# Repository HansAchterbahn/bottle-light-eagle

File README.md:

# Bottle Light: Eagle Data (PCB)

Bottle Light is a coaster that make your bottle glow in all colors of the rainbow. More information about the Bottle Light project can be found in the main repository: [bottle-light](https://github.com/HansAchterbahn/bottle-light)

In this Repository you can find the shematics and board layouts created in Eagle.

*Fork me and have fun!*

## Schematic

## Board

## 3D View (Fusion360)

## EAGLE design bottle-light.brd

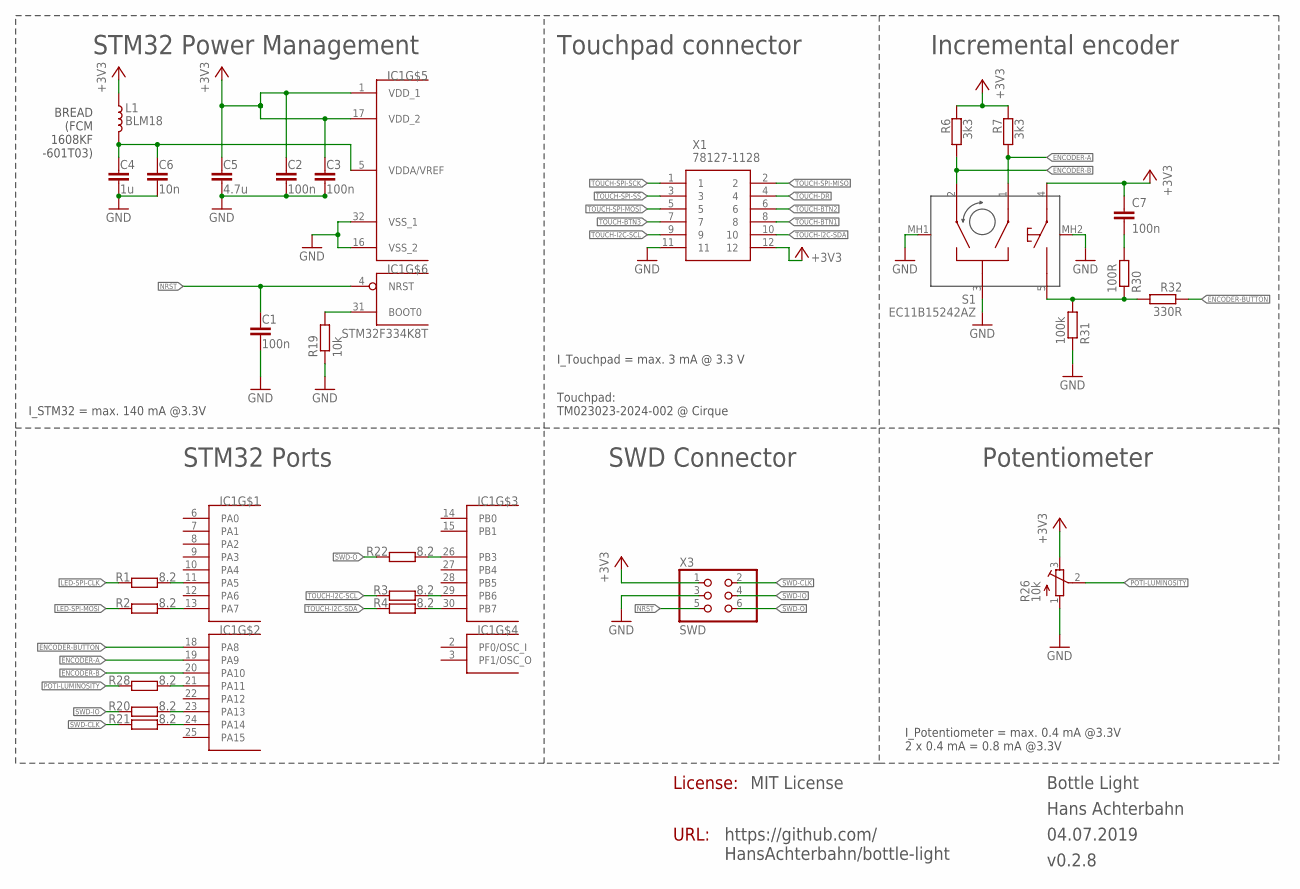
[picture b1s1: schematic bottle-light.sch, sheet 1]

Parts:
C1, C2, C3: 100n; C0603K
C4: 1u; C0603K
C5: 4.7u; C0603K
C6: 10n; C0603K
C7: 100n; C0603; MOUSER 581-0603YC104J
IC1: STM32F334K8T; LQFP32-7X7
L1: BLM18; L0603; MOUSER 81-BLM18KG601SN1D
R1, R2, R3, R4, R20, R21, R22, R28: 8.2; R0603
R6, R7: 3k3; R0603; MOUSER 71-CRCW06032K70FKEAC
R19: 10k; R0603
R26: 10k; RK0971110
R30: 100R; R0603; MOUSER 71-CRCW0603-100-E3
R31: 100k; R0603; MOUSER 71-CRCW0603-100K-E3
R32: 330R; R0603; MOUSER 71-CRCW0603-330-E3
S1: EC11B15242AZ; MPN EC11B15242AZ; MOUSER 688-EC11B15242AE
X1: 78127-1128; 781271128
X3: SWD; 2X03SMD; MOUSER 855-M20-8760342

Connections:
!TOUCH-SPI-SS: X1.3
+3V3: C2.1, C3.1, C5.1, C7.1, IC1.1 (VDD_1), IC1.17 (VDD_2), L1.1, R6.1, R7.1, R26.3 (E), S1.4 (D), X1.12, X3.1; also elsewhere on the board
ENCODER-A: IC1.19 (PA9), R7.2, S1.1 (A)
ENCODER-B: IC1.20 (PA10), R6.2, S1.2 (B)
ENCODER-BUTTON: IC1.18 (PA8), R32.1
GND: C1.2, C2.2, C3.2, C4.2, C5.2, C6.2, IC1.16 (VSS_2), IC1.32 (VSS_1), R19.1, R26.1 (A), R31.1, S1.3 (C), S1.MH1, S1.MH2, X1.11, X3.3; also elsewhere on the board
LED-SPI-CLK: R1.1; also elsewhere on the board
LED-SPI-MOSI: R2.1; also elsewhere on the board
unnamed: IC1.24 (PA14), R21.2
unnamed: IC1.11 (PA5), R1.2
unnamed: IC1.13 (PA7), R2.2
unnamed: IC1.29 (PB6), R3.2
unnamed: IC1.30 (PB7), R4.2
unnamed: IC1.21 (PA11), R28.2
unnamed: C4.1, C6.1, IC1.5 (VDDA/VREF), L1.2
unnamed: IC1.31 (BOOT0), R19.2
unnamed: IC1.23 (PA13), R20.2
unnamed: IC1.26 (PB3), R22.2
unnamed: R30.1, R31.2, R32.2, S1.5 (E)
unnamed: C7.2, R30.2
NRST: C1.1, IC1.4 (NRST), X3.5
POTI-LUMINOSITY: R26.2 (S), R28.1
SWD-CLK: R21.1, X3.2
SWD-IO: R20.1, X3.4
SWD-O: R22.1, X3.6
TOUCH-BTN1: X1.8
TOUCH-BTN2: X1.6
TOUCH-BTN3: X1.7
TOUCH-DR: X1.4
TOUCH-I2C-SCL: R3.1, X1.9
TOUCH-I2C-SDA: R4.1, X1.10
TOUCH-SPI-MISO: X1.2
TOUCH-SPI-MOSI: X1.5
TOUCH-SPI-SCK: X1.1

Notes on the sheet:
STM32 Power Management
STM32 Ports
Incremental encoder
SWD Connector
Potentiometer
I_Potentiometer = max. 0.4 mA @3.3V 2 x 0.4 mA = 0.8 mA @3.3V
I_STM32 = max. 140 mA @3.3V
License:
BREAD (FCM 1608KF -601T03)
Touchpad connector
I_Touchpad = max. 3 mA @ 3.3 V
Touchpad: TM023023-2024-002 @ Cirque
https://github.com/ HansAchterbahn/bottle-light
URL:

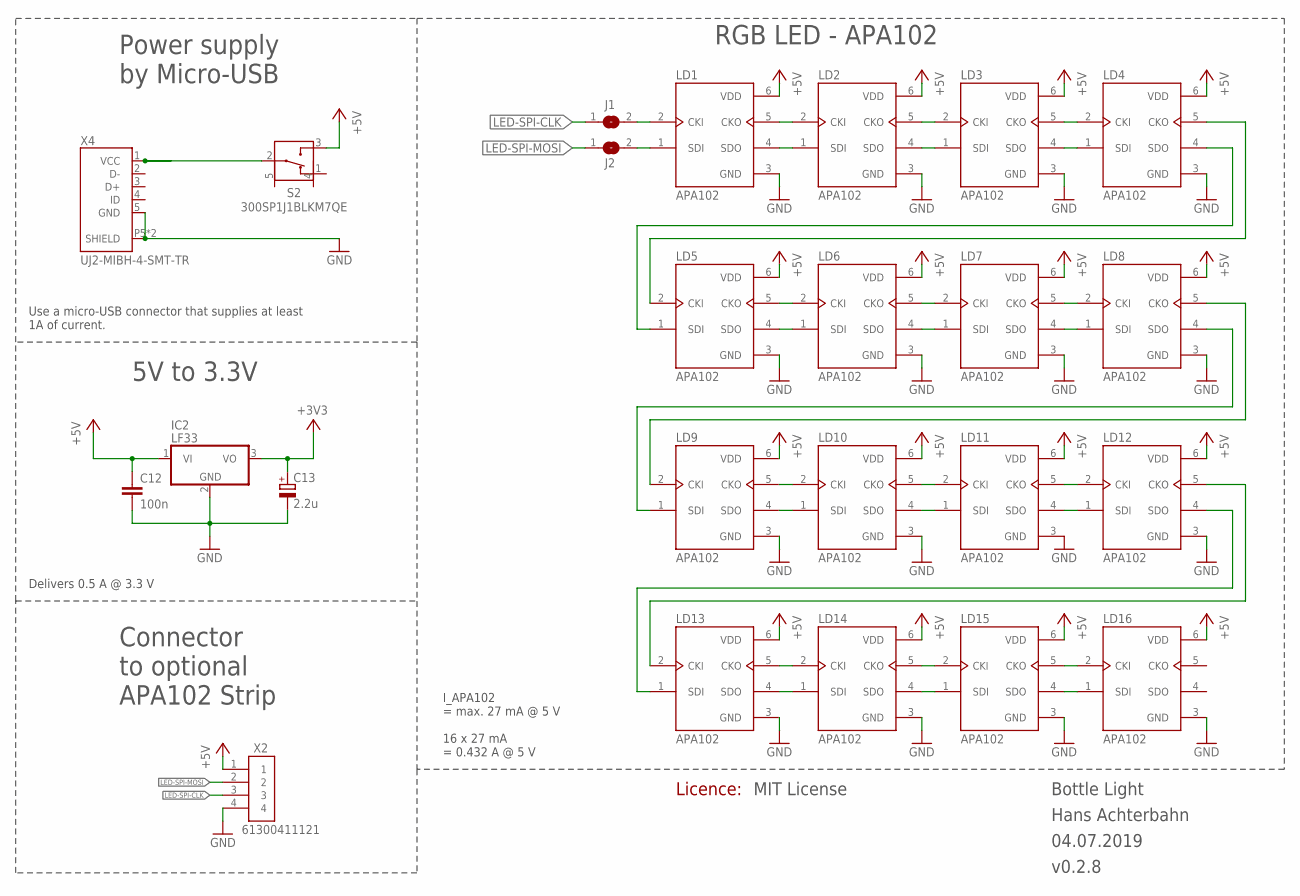
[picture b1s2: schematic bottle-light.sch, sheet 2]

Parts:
C12: 100n; C0603
C13: 2.2u; 153CLV-0505
IC2: LF33; TO220H
J1, J2: SJ
LD1, LD2, LD3, LD4, LD5, LD6, LD7, LD8, LD9, LD10, LD11, LD12, LD13, LD14, LD15, LD16: APA102; APA102C-5050
S2: 300SP1J1BLKM7QE
X2: 61300411121
X4: UJ2-MIBH-4-SMT-TR; CUIINC_UJ2-MIBH-4-SMT-TR-2; MOUSER 490-UJ2-MIBH-4-SMT

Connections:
5V-IN: S2.2 (IN), X4.1 (VCC)
+3V3: C13.+, IC2.3 (VO); also elsewhere on the board
+5V: C12.1, IC2.1 (VI), LD1.6 (VDD), LD2.6 (VDD), LD3.6 (VDD), LD4.6 (VDD), LD5.6 (VDD), LD6.6 (VDD), LD7.6 (VDD), LD8.6 (VDD), LD9.6 (VDD), LD10.6 (VDD), LD11.6 (VDD), LD12.6 (VDD), LD13.6 (VDD), LD14.6 (VDD), LD15.6 (VDD), LD16.6 (VDD), S2.3 (OUT1), X2.1
GND: C12.2, C13.-, IC2.2 (GND), LD1.3 (GND), LD2.3 (GND), LD3.3 (GND), LD4.3 (GND), LD5.3 (GND), LD6.3 (GND), LD7.3 (GND), LD8.3 (GND), LD9.3 (GND), LD10.3 (GND), LD11.3 (GND), LD12.3 (GND), LD13.3 (GND), LD14.3 (GND), LD15.3 (GND), LD16.3 (GND), X2.4, X4.5 (GND), X4.P5 (SHIELD), X4.P6 (SHIELD); also elsewhere on the board
LED-SPI-CLK: J1.1, X2.3; also elsewhere on the board
LED-SPI-MOSI: J2.1, X2.2; also elsewhere on the board
unnamed: J1.2, LD1.2 (CKI)
unnamed: J2.2, LD1.1 (SDI)
unnamed: LD1.5 (CKO), LD2.2 (CKI)
unnamed: LD1.4 (SDO), LD2.1 (SDI)
unnamed: LD2.5 (CKO), LD3.2 (CKI)
unnamed: LD2.4 (SDO), LD3.1 (SDI)
unnamed: LD3.5 (CKO), LD4.2 (CKI)
unnamed: LD3.4 (SDO), LD4.1 (SDI)
unnamed: LD4.5 (CKO), LD5.2 (CKI)
unnamed: LD4.4 (SDO), LD5.1 (SDI)
unnamed: LD5.5 (CKO), LD6.2 (CKI)
unnamed: LD5.4 (SDO), LD6.1 (SDI)
unnamed: LD6.5 (CKO), LD7.2 (CKI)
unnamed: LD6.4 (SDO), LD7.1 (SDI)
unnamed: LD7.5 (CKO), LD8.2 (CKI)
unnamed: LD7.4 (SDO), LD8.1 (SDI)
unnamed: LD8.5 (CKO), LD9.2 (CKI)
unnamed: LD8.4 (SDO), LD9.1 (SDI)
unnamed: LD9.5 (CKO), LD10.2 (CKI)
unnamed: LD9.4 (SDO), LD10.1 (SDI)
unnamed: LD10.5 (CKO), LD11.2 (CKI)
unnamed: LD10.4 (SDO), LD11.1 (SDI)
unnamed: LD11.5 (CKO), LD12.2 (CKI)
unnamed: LD11.4 (SDO), LD12.1 (SDI)
unnamed: LD12.5 (CKO), LD13.2 (CKI)
unnamed: LD12.4 (SDO), LD13.1 (SDI)
unnamed: LD13.5 (CKO), LD14.2 (CKI)
unnamed: LD13.4 (SDO), LD14.1 (SDI)
unnamed: LD14.5 (CKO), LD15.2 (CKI)
unnamed: LD14.4 (SDO), LD15.1 (SDI)
unnamed: LD15.5 (CKO), LD16.2 (CKI)
unnamed: LD15.4 (SDO), LD16.1 (SDI)

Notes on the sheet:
Power supply by Micro-USB
5V to 3.3V
RGB LED - APA102
Delivers 0.5 A @ 3.3 V
Use a micro-USB connector that supplies at least 1A of current.
I_APA102 = max. 27 mA @ 5 V 16 x 27 mA = 0.432 A @ 5 V
Licence:
Connector to optional APA102 Strip

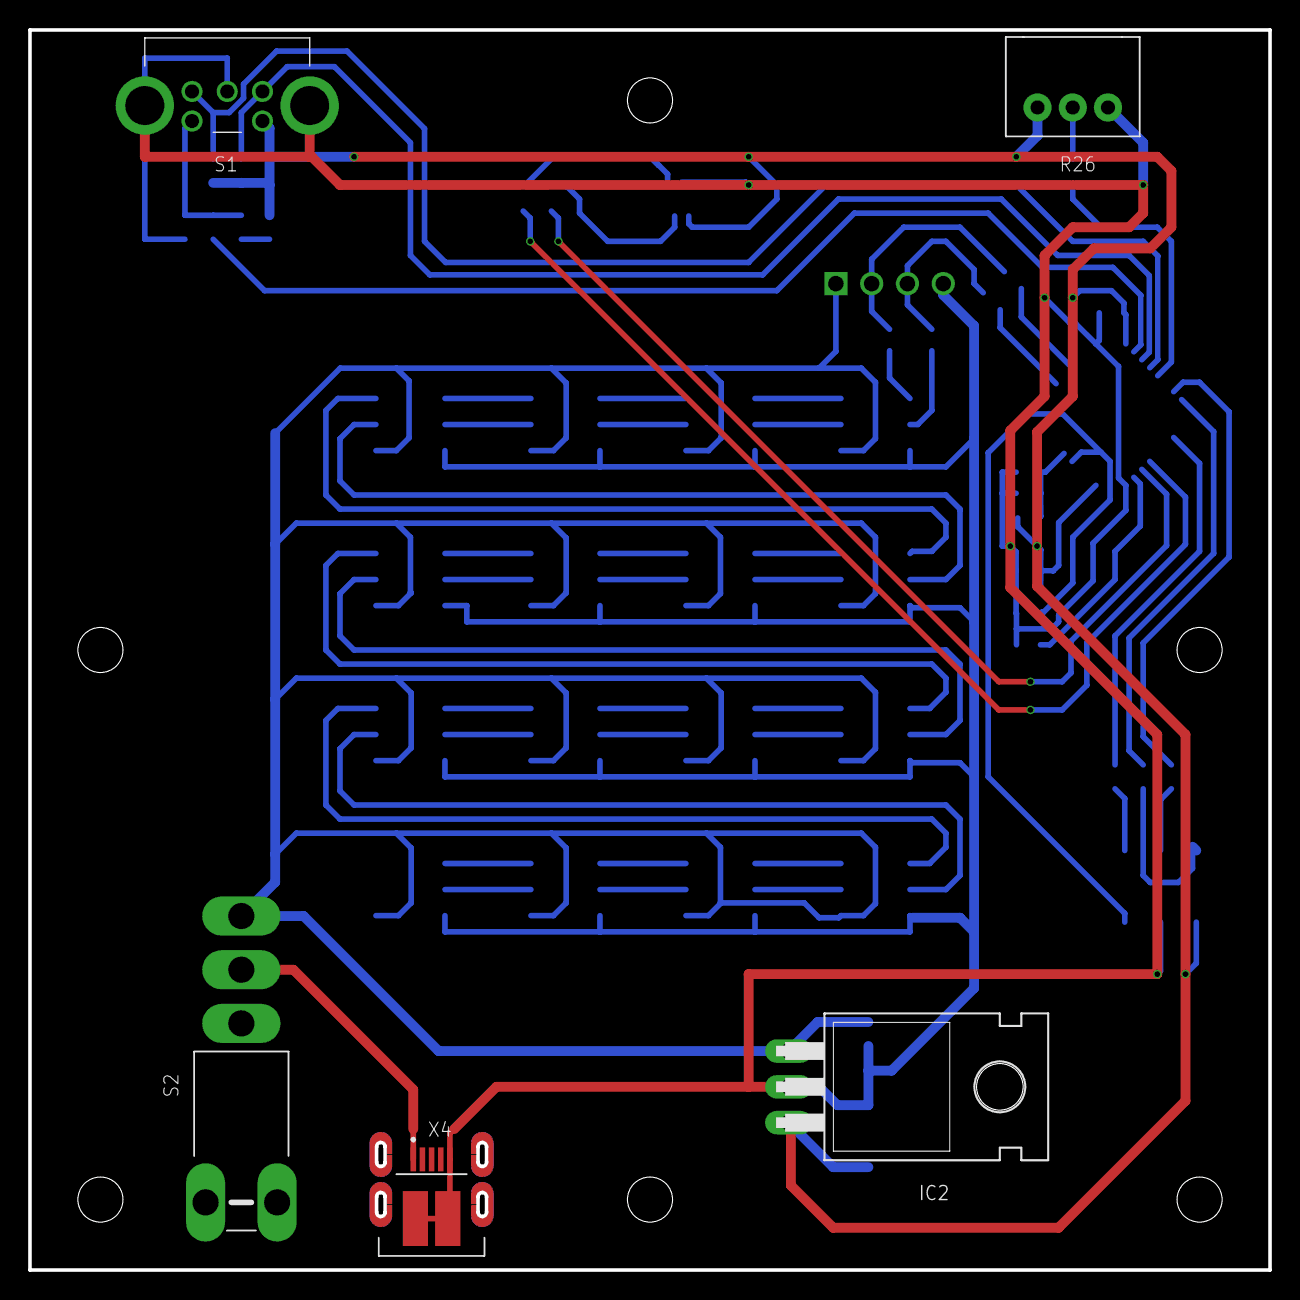
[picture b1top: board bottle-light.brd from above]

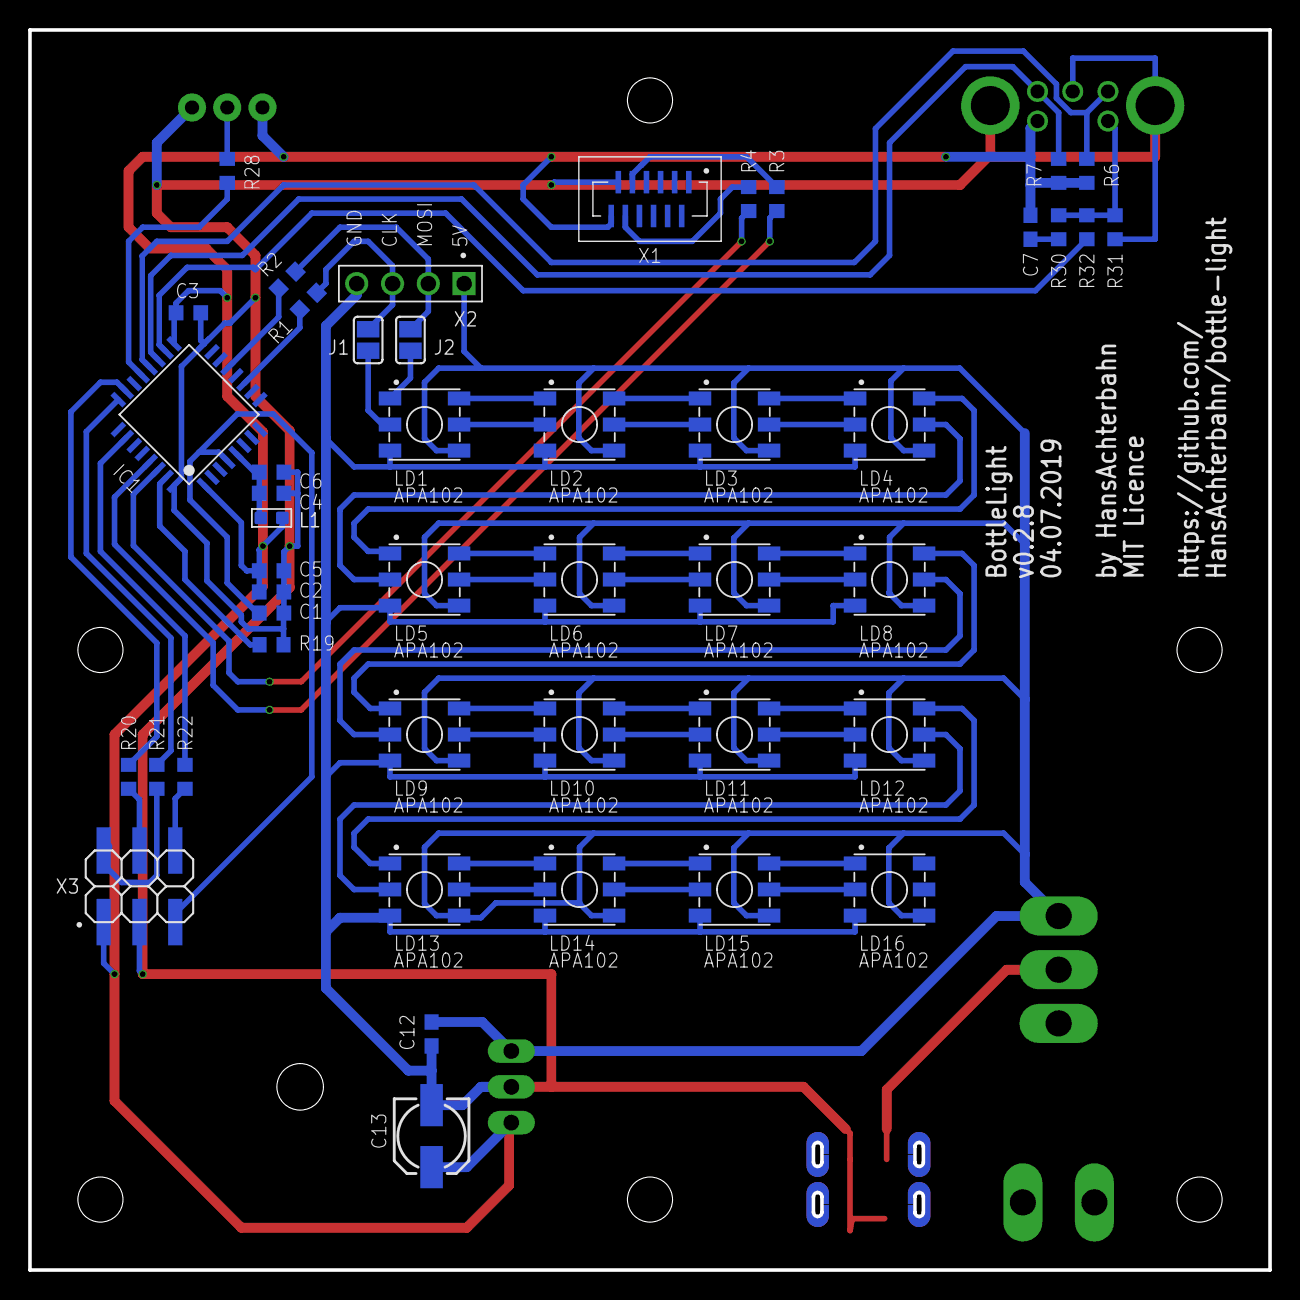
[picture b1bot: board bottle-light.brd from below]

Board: 2 copper layers, 88.0 x 88.0 mm, 52 parts (46 on the bottom side), 60 nets.

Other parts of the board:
U$1: A4L-LOC

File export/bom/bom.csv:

Qty;Value;Device;Package;Parts;Description;ALLIED_NUMBER;ALLIED_PRICE-STOCK;CREATED_BY;DESCRIPTION;DIGI_KEY_PART_NUMBER;HEIGHT;MANUFACTURER;MF;MFN;MOUSER;RS-ONLINE
2;;SJ;SJ;J1, J2;SMD solder JUMPER;;;;;;;;;;;
1;100R;R-EU_R0603;R0603;R30;RESISTOR, European symbol;;;;;;;;Vishay;CRCW0603100RFKEAHP;71-CRCW0603-100-E3;820-6748
1;100k;R-EU_R0603;R0603;R31;RESISTOR, European symbol;;;;;;;;Vishay;CRCW0603100KFKEA;71-CRCW0603-100K-E3;678-9673 
1;100n;C-EUC0603;C0603;C7;CAPACITOR, European symbol;;;;;;;;AVX;0603YC104JAT2A;581-0603YC104J;391-246 
1;100n;C-EUC0603;C0603;C12;CAPACITOR, European symbol;;;;;;;;;;;
3;100n;C-EUC0603K;C0603K;C1, C2, C3;CAPACITOR, European symbol;;;;;;;;;;;391-246
1;10k;R-EU_R0603;R0603;R19;RESISTOR, European symbol;;;;;;;;;;;
1;10k;RK0971110;RK0971110;R26;Potentiometer;;;;;;;;ALPS;RK097111080R;688-RK097111080R;729-3458
1;10n;C-EUC0603K;C0603K;C6;CAPACITOR, European symbol;;;;;;;;;;;264-4595
1;1u;C-EUC0603K;C0603K;C4;CAPACITOR, European symbol;;;;;;;;;;;435-1403
1;2.2u;CPOL-EU153CLV-0505;153CLV-0505;C13;POLARIZED CAPACITOR, European symbol;;;;;;;;;;;
1;300SP1J1BLKM7QE;300SP1J1BLKM7QE;300SP1J1BLKM7QE;S2;E-Switch - 300 Series Rocker Switch;;;;;;;;E-Switch;300SP1J1BLKM7QE;612-300SP1J1BLKM7QE ;-
1;330R;R-EU_R0603;R0603;R32;RESISTOR, European symbol;;;;;;;;Vishay;CRCW0603330RFKEA;71-CRCW0603-330-E3;679-0226
2;3k3;R-EU_R0603;R0603;R6, R7;RESISTOR, European symbol;;;;;;;;Vishay;CRCW06032K70FKEAC;71-CRCW06032K70FKEAC;-
1;4.7u;C-EUC0603K;C0603K;C5;CAPACITOR, European symbol;;;;;;;;;;;691-1164
1;61300411121;61300411121;61300411121;X2;CONN HEADER VERT 4POS 2.54MM;;;PCBLayout.com;;732-5317-ND;;Wurth Electronics Inc.;;61300411121;;
1;78127-1128;78127-1128;781271128;X1;FFC & FPC Connectors 0.5 FPC CONN. VERTIC AL SMT NON-ZIF 12CKT;70714305;https://www.alliedelec.com/molex-incorporated-78127-1128/70714305/;;FFC & FPC Connectors 0.5 FPC CONN. VERTIC AL SMT NON-ZIF 12CKT;;4mm;;Molex;78127-1128;538-78127-1128;
8;8.2;R-EU_R0603;R0603;R1, R2, R3, R4, R20, R21, R22, R28;RESISTOR, European symbol;;;;;;;;;;;904-5027
16;APA102;APA102APA102C-5050;APA102C-5050;LD1 … LD16;DotStar Micro LEDs (APA102–2020)- Smart SMD RGB LED - 100 pack;;;;;;;;;;;
1;BLM18;INDUCTOR/FERRITE-BEAD'0603';L0603;L1;;;;;;;;;Murata;BLM18KG601SN1D;81-BLM18KG601SN1D;747-4720
1;EC11B15242AZ;EC11B15242AZ;EC11B15242AZ;S1;Komponente von www.SamacSys.com geforkt:;;;;Encoders 5 Volts Through Hole;;24mm;;ALPS;EC11B15242AZ;688-EC11B15242AE;
1;LF33;7805T;TO220H;IC2;Positive VOLTAGE REGULATOR;;;;;;;;;;;
1;STM32F334K8T;STM32F334K8T;LQFP32-7X7;IC1;STM32 Mikrocontroller: STM32F334K8Tx;;;;;;;;ST;STM32F334K8T;;
1;SWD;PINHD-2X3_2.54-SMD;2X03SMD;X3;PIN HEADER;;;;;;;;Harwin;M20-8760342;855-M20-8760342;681-2880
1;UJ2-MIBH-4-SMT-TR;UJ2-MIBH-4-SMT-TRCUIINC_UJ2-MIBH-4-SMT-TR-2;CUIINC_UJ2-MIBH-4-SMT-TR-2;X4;Micro B Type 5 Pin Horizontal 30 µin Plating SMT USB Jack 2.0;;;;;;;;;;;

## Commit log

2017-07-02 v0.1.0 created new projet 'bottle-light'
2017-07-03 v0.1.1 worked on circuit diagram - new push buttons - new on/off button
2017-07-09 v0.1.2 Put in new devices and began routing pcb - new potis - made groundplane size for case - placed leds, potis and switch
2017-07-09 v0.1.3 schematic finished and board is routed - added new buttons - added swd debugger port - added battery pack - changed stm32 pinning - changed dc power supply port - removed reset button - added 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
2018-10-12 v0.1.4 new schematic arrangement
2019-01-05 v0.2.0 Neue LEDs hinzugefügt: APA102
2019-01-05 v0.2.1 Die neuen LEDs positioniert
2019-06-08 v0.2.2 LEDs connected and port for touch pad added
2019-06-09 Added datasheets for APA102 and TM023023 touch pad
2019-06-09 v0.2.3 pinout and connection of touch pad to STM32 | changed library of buttons and potentiometers | added polygon on top and bottom| changed Micro-USB position
2019-06-10 v0.2.4 Device of Micro-USB connector was defect -> repaired | removed buttons and color potentiometer | added incremental encoder | connected touch pad connector to I2C of STM32 | added MIT license |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
2019-06-10 Update LICENSE
2019-06-11 v0.2.5 changed luminosity potentiometer | potentiometer and incremental encoder set to correct position
2019-06-11 v0.2.6 STM32 rotated 45 degrees to optimize wire routing.
2019-06-13 v0.2.7 new power switch | new restricted areas | optimized wires | checked positions of all components mounted at the edge | optimized polygon
2019-06-19 optimized text positions | added 2 jumpers for easy usage of additional LED strip
2019-06-27 Vias verkleinert | 3D Modelle hinzugefügt | auf Fusion gepusht
2019-06-27 Gerber Daten erzeugt und 5 weiße Prototyp + Stencil bei https://jlcpcb.com bestellt ($ 20.46)
2019-06-27 Fusion sync
2019-07-01 Update README | added images of schematic, board and 3D view
2019-07-04 changed some footprint drawings
2019-07-20 added todo tasks
2019-07-20 added bom files
2019-07-20 added datasheets
2019-07-20 added attributes to UJ2-MIBH-4-SMT-TR
2019-11-14 Added a 3d package and a 3d model of the PCB

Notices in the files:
bottle-light.brd:
MIT Licence
bottle-light.sch:
LICENSE: MIT License
